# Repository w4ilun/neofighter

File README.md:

# NeoFighter

Build your own NeoFighter! Powered by the Atmega32u4 (Arduino support) and 32 RGB LEDs. Custom PCB (no messy wiring).

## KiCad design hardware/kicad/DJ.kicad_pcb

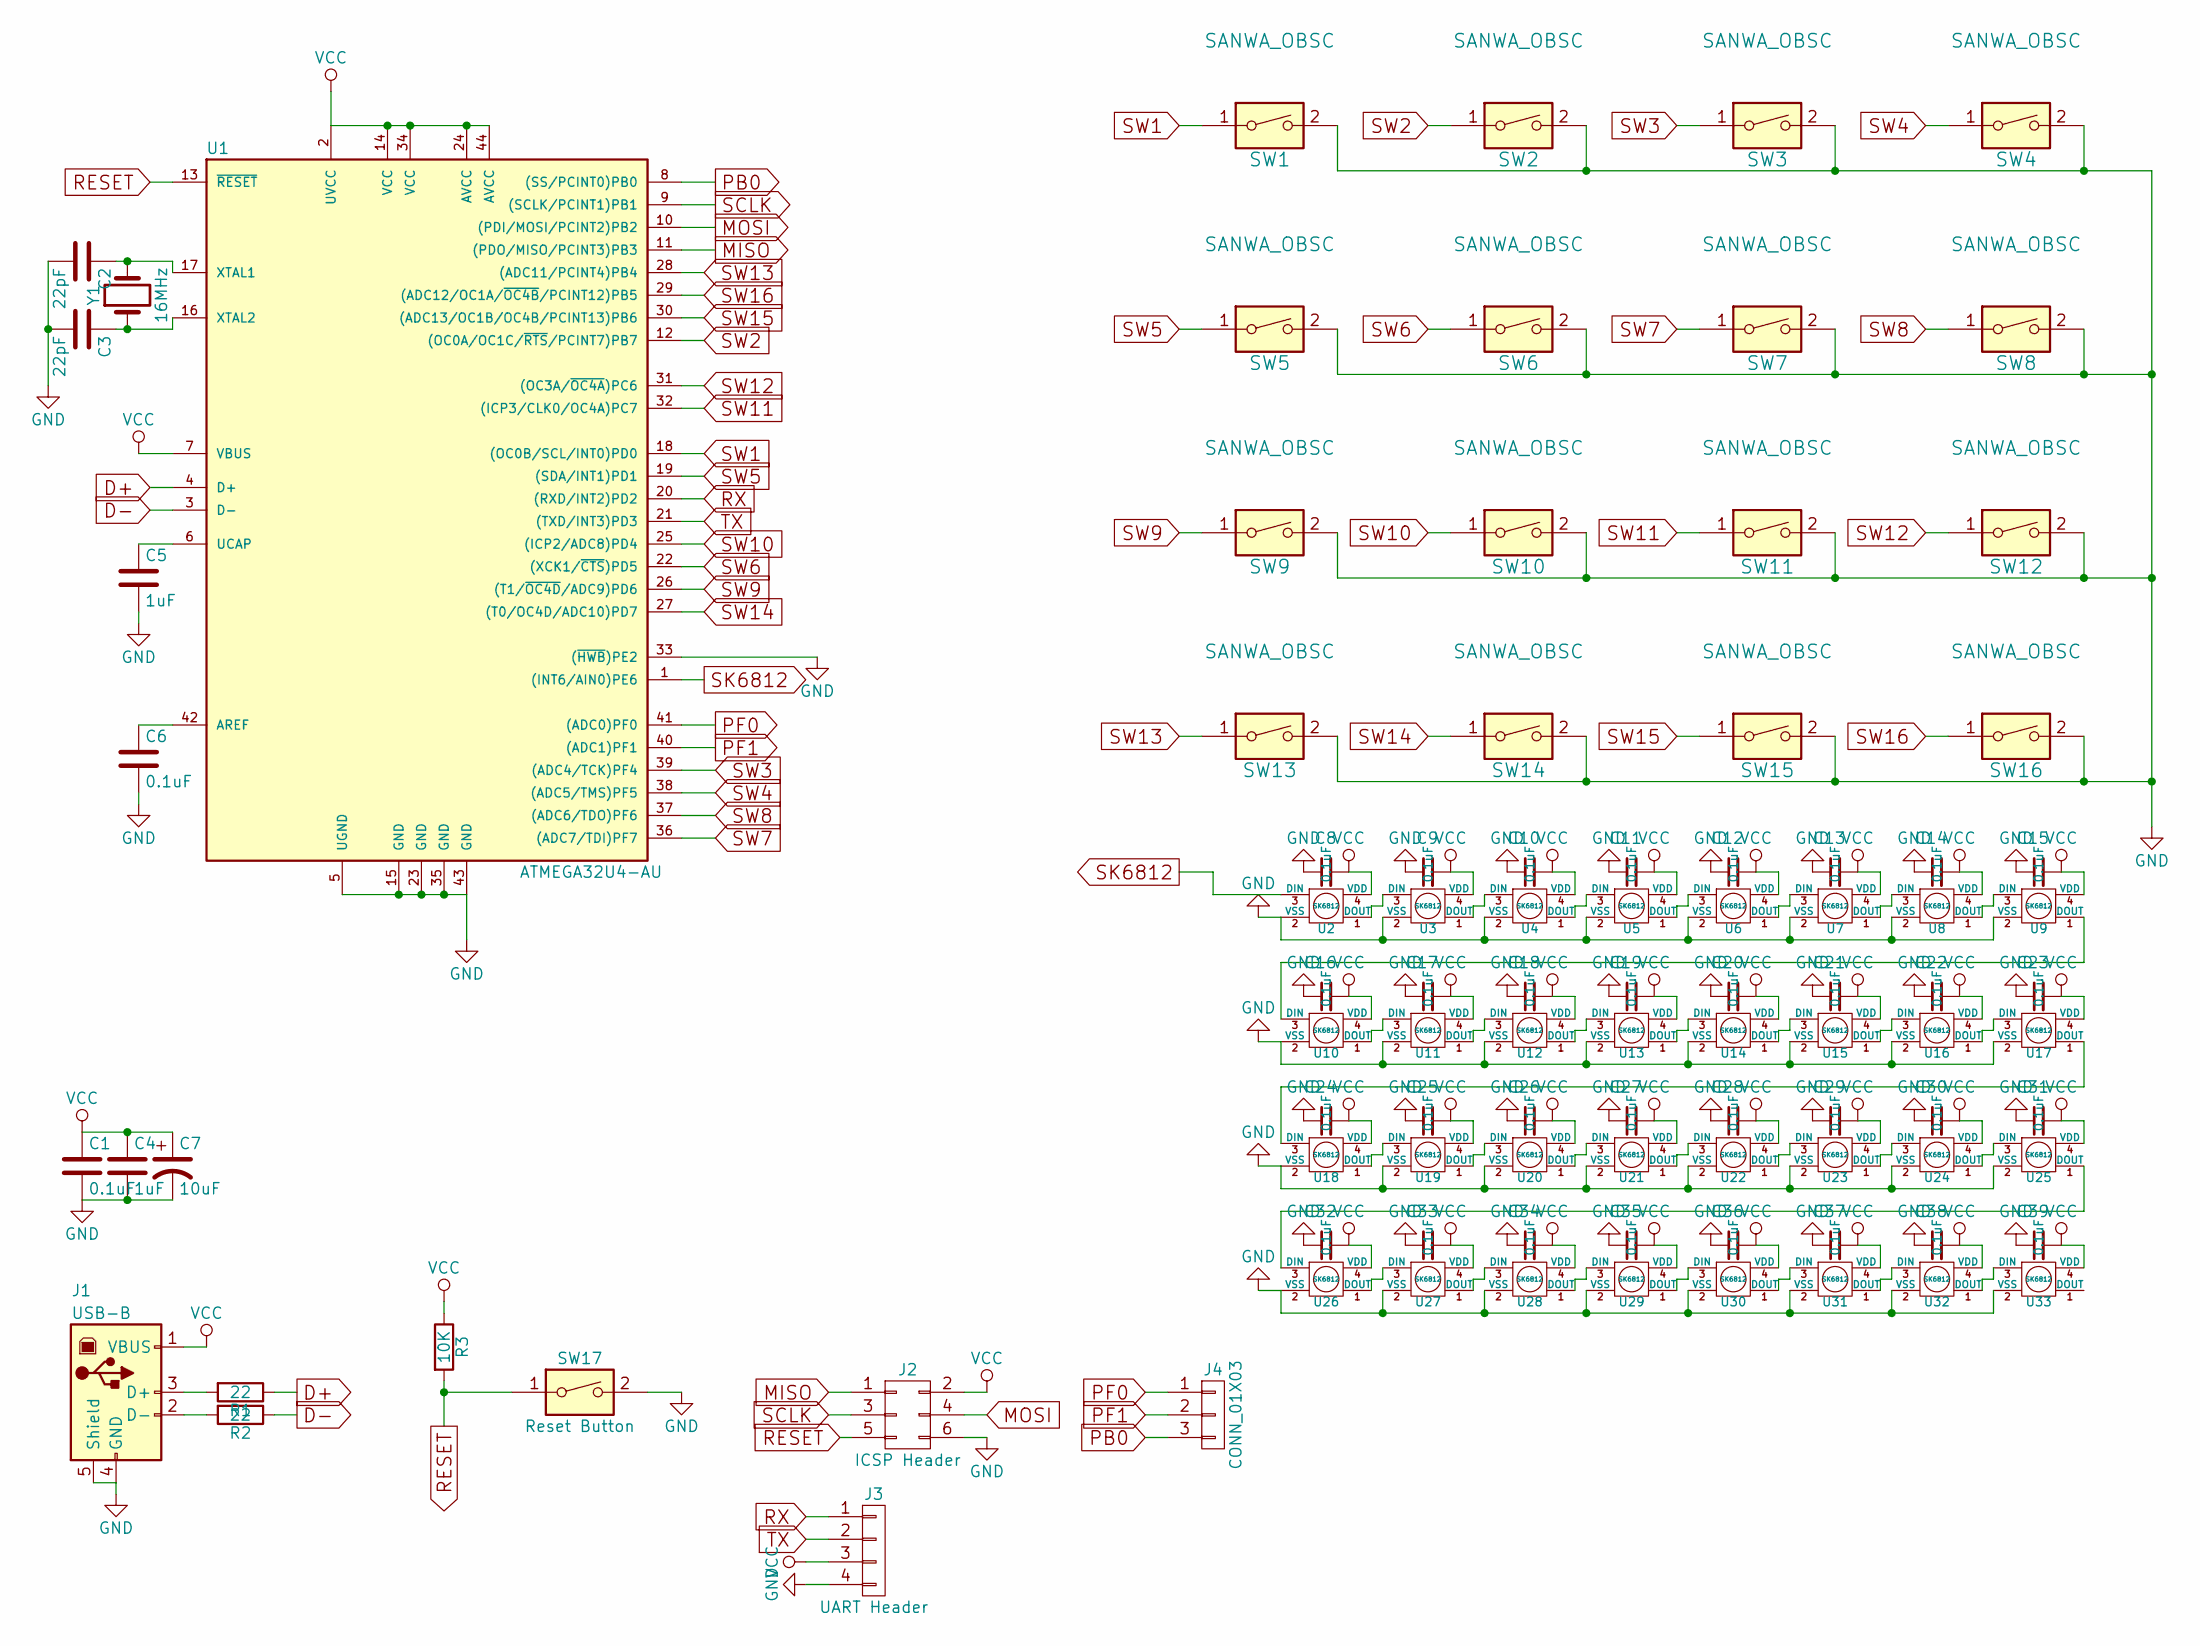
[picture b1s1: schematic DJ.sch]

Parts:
C1, C6, C8, C9, C10, C11, C12, C13, C14, C15, C16, C17, C18, C19, C20, C21, C22, C23, C24, C25, C26, C27, C28, C29, C30, C31, C32, C33, C34, C35, C36, C37, C38, C39: 0.1uF; C_0805_HandSoldering
C2, C3: 22pF; C_0805_HandSoldering
C4, C5: 1uF; C_0805_HandSoldering
C7: 10uF; C_0805_HandSoldering
J1: USB-B; USB_B
J2: ICSP Header; Pin_Header_Straight_2x03_Pitch2.54mm
J3: UART Header; Pin_Header_Straight_1x04_Pitch2.54mm
J4: CONN_01X03; Pin_Header_Straight_1x03_Pitch2.54mm
R1, R2: 22; R_0805_HandSoldering
R3: 10K; R_0805_HandSoldering
SW1, SW2, SW3, SW4, SW5, SW6, SW7, SW8, SW9, SW10, SW11, SW12, SW13, SW14, SW15, SW16: SANWA_OBSC
SW17: Reset Button; SW_SPST_TL3342
U1: ATMEGA32U4-AU; TQFP-44_10x10mm_Pitch0.8mm
U2, U3, U4, U5, U6, U7, U8, U9, U10, U11, U12, U13, U14, U15, U16, U17, U18, U19, U20, U21, U22, U23, U24, U25, U26, U27, U28, U29, U30, U31, U32, U33: SK6812; SK6812_3535
Y1: 16MHz; Crystal_SMD_Abracon_ABM3-2pin_5.0x3.2mm_HandSoldering

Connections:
D+: R1.1, U1.4 (D+)
D-: R2.1, U1.3 (D-)
GND: C1.2, C2.2, C3.2, C4.2, C5.2, C6.2, C7.2, C8.1, C9.1, C10.1, C11.1, C12.1, C13.1, C14.1, C15.1, C16.1, C17.1, C18.1, C19.1, C20.1, C21.1, C22.1, C23.1, C24.1, C25.1, C26.1, C27.1, C28.1, C29.1, C30.1, C31.1, C32.1, C33.1, C34.1, C35.1, C36.1, C37.1, C38.1, C39.1, J1.4 (GND), J1.5 (Shield), J2.6, J3.4, SW1.2, SW2.2, SW3.2, SW4.2, SW5.2, SW6.2, SW7.2, SW8.2, SW9.2, SW10.2, SW11.2, SW12.2, SW13.2, SW14.2, SW15.2, SW16.2, SW17.2, U1.5 (UGND), U1.15 (GND), U1.23 (GND), U1.33 ((~HWB~)PE2), U1.35 (GND), U1.43 (GND), U2.2 (VSS), U3.2 (VSS), U4.2 (VSS), U5.2 (VSS), U6.2 (VSS), U7.2 (VSS), U8.2 (VSS), U9.2 (VSS), U10.2 (VSS), U11.2 (VSS), U12.2 (VSS), U13.2 (VSS), U14.2 (VSS), U15.2 (VSS), U16.2 (VSS), U17.2 (VSS), U18.2 (VSS), U19.2 (VSS), U20.2 (VSS), U21.2 (VSS), U22.2 (VSS), U23.2 (VSS), U24.2 (VSS), U25.2 (VSS), U26.2 (VSS), U27.2 (VSS), U28.2 (VSS), U29.2 (VSS), U30.2 (VSS), U31.2 (VSS), U32.2 (VSS), U33.2 (VSS)
MISO: J2.1, U1.11 ((PDO/MISO/PCINT3)PB3)
MOSI: J2.4, U1.10 ((PDI/MOSI/PCINT2)PB2)
unnamed: C2.1, U1.17 (XTAL1), Y1.2
unnamed: C3.1, U1.16 (XTAL2), Y1.1
unnamed: C5.1, U1.6 (UCAP)
unnamed: C6.1, U1.42 (AREF)
unnamed: J1.2 (D-), R2.2
unnamed: J1.3 (D+), R1.2
unnamed: U2.1 (DOUT), U3.3 (DIN)
unnamed: U3.1 (DOUT), U4.3 (DIN)
unnamed: U4.1 (DOUT), U5.3 (DIN)
unnamed: U5.1 (DOUT), U6.3 (DIN)
unnamed: U6.1 (DOUT), U7.3 (DIN)
unnamed: U7.1 (DOUT), U8.3 (DIN)
unnamed: U8.1 (DOUT), U9.3 (DIN)
unnamed: U10.1 (DOUT), U11.3 (DIN)
unnamed: U9.1 (DOUT), U10.3 (DIN)
unnamed: U11.1 (DOUT), U12.3 (DIN)
unnamed: U12.1 (DOUT), U13.3 (DIN)
unnamed: U13.1 (DOUT), U14.3 (DIN)
unnamed: U14.1 (DOUT), U15.3 (DIN)
unnamed: U15.1 (DOUT), U16.3 (DIN)
unnamed: U16.1 (DOUT), U17.3 (DIN)
unnamed: U17.1 (DOUT), U18.3 (DIN)
unnamed: U18.1 (DOUT), U19.3 (DIN)
unnamed: U19.1 (DOUT), U20.3 (DIN)
unnamed: U20.1 (DOUT), U21.3 (DIN)
unnamed: U21.1 (DOUT), U22.3 (DIN)
unnamed: U22.1 (DOUT), U23.3 (DIN)
unnamed: U23.1 (DOUT), U24.3 (DIN)
unnamed: U24.1 (DOUT), U25.3 (DIN)
unnamed: U25.1 (DOUT), U26.3 (DIN)
unnamed: U26.1 (DOUT), U27.3 (DIN)
unnamed: U27.1 (DOUT), U28.3 (DIN)
unnamed: U28.1 (DOUT), U29.3 (DIN)
unnamed: U29.1 (DOUT), U30.3 (DIN)
unnamed: U30.1 (DOUT), U31.3 (DIN)
unnamed: U31.1 (DOUT), U32.3 (DIN)
unnamed: U32.1 (DOUT), U33.3 (DIN)
PB0: J4.3, U1.8 ((SS/PCINT0)PB0)
PF0: J4.1, U1.41 ((ADC0)PF0)
PF1: J4.2, U1.40 ((ADC1)PF1)
RESET: J2.5, R3.2, SW17.1, U1.13 (~RESET~)
RX: J3.1, U1.20 ((RXD/INT2)PD2)
SCLK: J2.3, U1.9 ((SCLK/PCINT1)PB1)
SK6812: U1.1 ((INT6/AIN0)PE6), U2.3 (DIN)
SW1: SW1.1, U1.18 ((OC0B/SCL/INT0)PD0)
SW2: SW2.1, U1.12 ((OC0A/OC1C/~RTS~/PCINT7)PB7)
SW3: SW3.1, U1.39 ((ADC4/TCK)PF4)
SW4: SW4.1, U1.38 ((ADC5/TMS)PF5)
SW5: SW5.1, U1.19 ((SDA/INT1)PD1)
SW6: SW6.1, U1.22 ((XCK1/~CTS~)PD5)
SW7: SW7.1, U1.36 ((ADC7/TDI)PF7)
SW8: SW8.1, U1.37 ((ADC6/TDO)PF6)
SW9: SW9.1, U1.26 ((T1/~OC4D~/ADC9)PD6)
SW10: SW10.1, U1.25 ((ICP2/ADC8)PD4)
SW11: SW11.1, U1.32 ((ICP3/CLK0/OC4A)PC7)
SW12: SW12.1, U1.31 ((OC3A/~OC4A~)PC6)
SW13: SW13.1, U1.28 ((ADC11/PCINT4)PB4)
SW14: SW14.1, U1.27 ((T0/OC4D/ADC10)PD7)
SW15: SW15.1, U1.30 ((ADC13/OC1B/OC4B/PCINT13)PB6)
SW16: SW16.1, U1.29 ((ADC12/OC1A/~OC4B~/PCINT12)PB5)
TX: J3.2, U1.21 ((TXD/INT3)PD3)
VCC: C1.1, C4.1, C7.1, C8.2, C9.2, C10.2, C11.2, C12.2, C13.2, C14.2, C15.2, C16.2, C17.2, C18.2, C19.2, C20.2, C21.2, C22.2, C23.2, C24.2, C25.2, C26.2, C27.2, C28.2, C29.2, C30.2, C31.2, C32.2, C33.2, C34.2, C35.2, C36.2, C37.2, C38.2, C39.2, J1.1 (VBUS), J2.2, J3.3, R3.1, U1.2 (UVCC), U1.7 (VBUS), U1.14 (VCC), U1.24 (AVCC), U1.34 (VCC), U1.44 (AVCC), U2.4 (VDD), U3.4 (VDD), U4.4 (VDD), U5.4 (VDD), U6.4 (VDD), U7.4 (VDD), U8.4 (VDD), U9.4 (VDD), U10.4 (VDD), U11.4 (VDD), U12.4 (VDD), U13.4 (VDD), U14.4 (VDD), U15.4 (VDD), U16.4 (VDD), U17.4 (VDD), U18.4 (VDD), U19.4 (VDD), U20.4 (VDD), U21.4 (VDD), U22.4 (VDD), U23.4 (VDD), U24.4 (VDD), U25.4 (VDD), U26.4 (VDD), U27.4 (VDD), U28.4 (VDD), U29.4 (VDD), U30.4 (VDD), U31.4 (VDD), U32.4 (VDD), U33.4 (VDD)

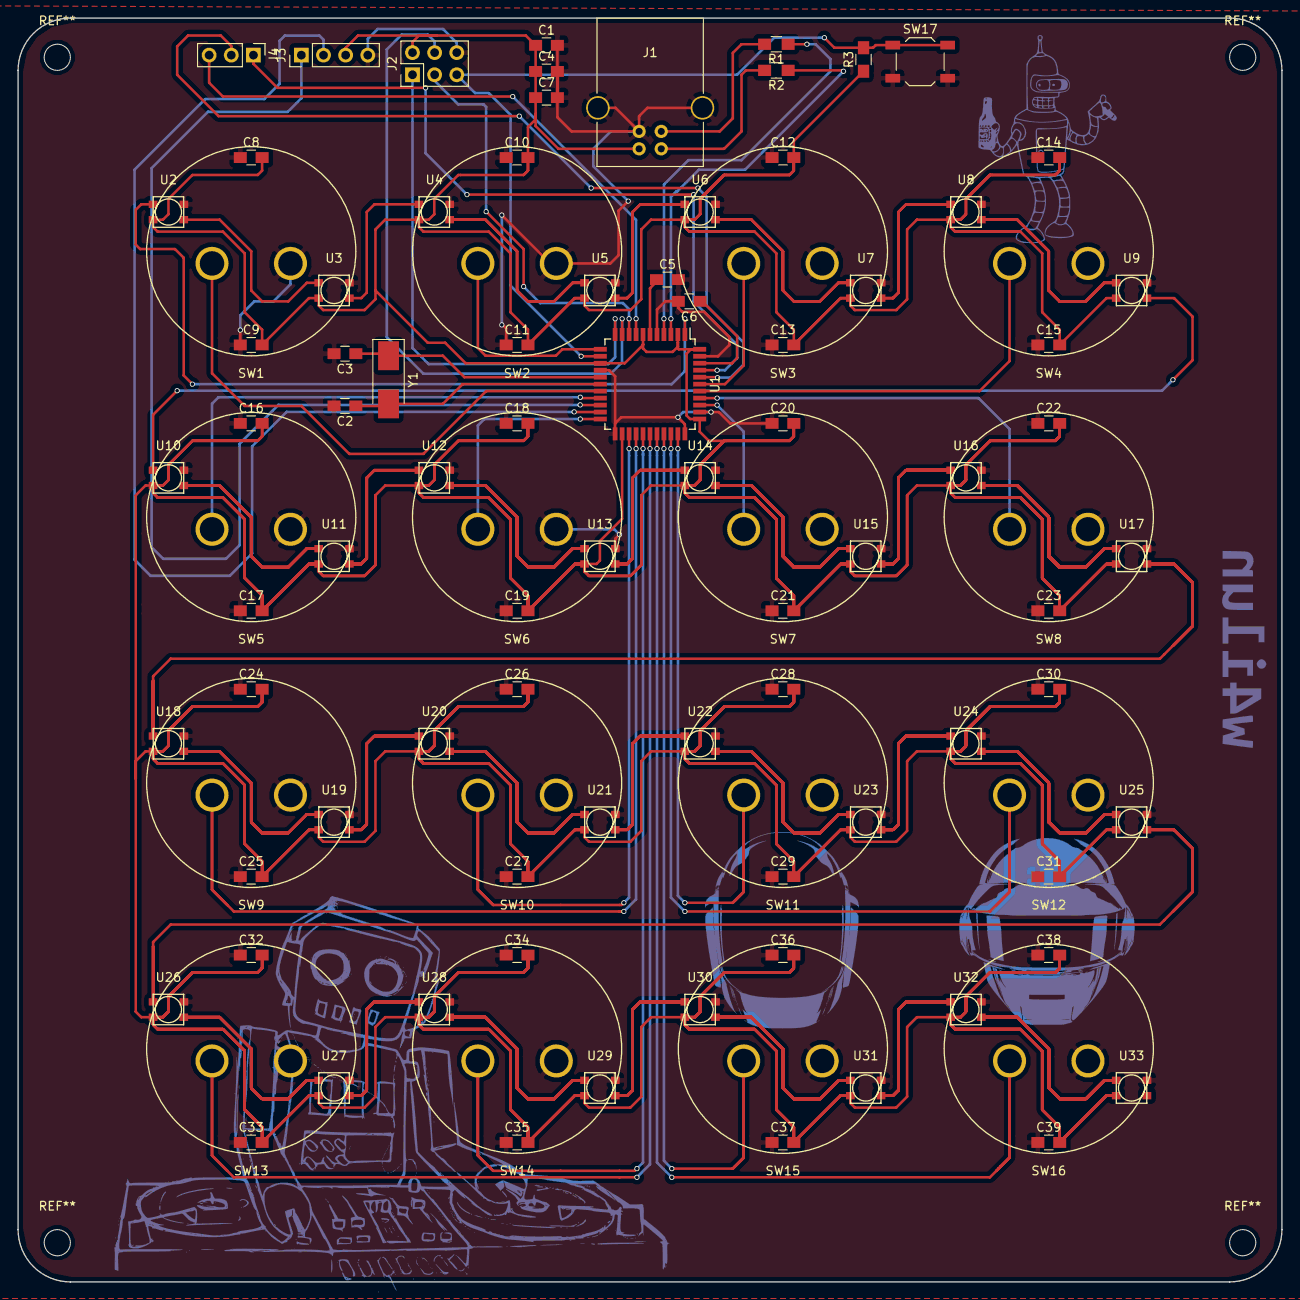
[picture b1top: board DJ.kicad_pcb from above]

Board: 2 copper layers, 145.0 x 145.0 mm, 97 parts (0 on the bottom side), 67 nets.

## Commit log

2017-09-10 added READMEs
2017-09-10 added ino
2017-09-10 added GERBERS
2017-09-10 added enclosure files
2017-09-10 added schematic
2017-10-01 added image
2017-10-01 wrong markdown syntax
2017-10-01 brief intro
2018-01-24 Rename midifighter.ino to neofighter.ino
